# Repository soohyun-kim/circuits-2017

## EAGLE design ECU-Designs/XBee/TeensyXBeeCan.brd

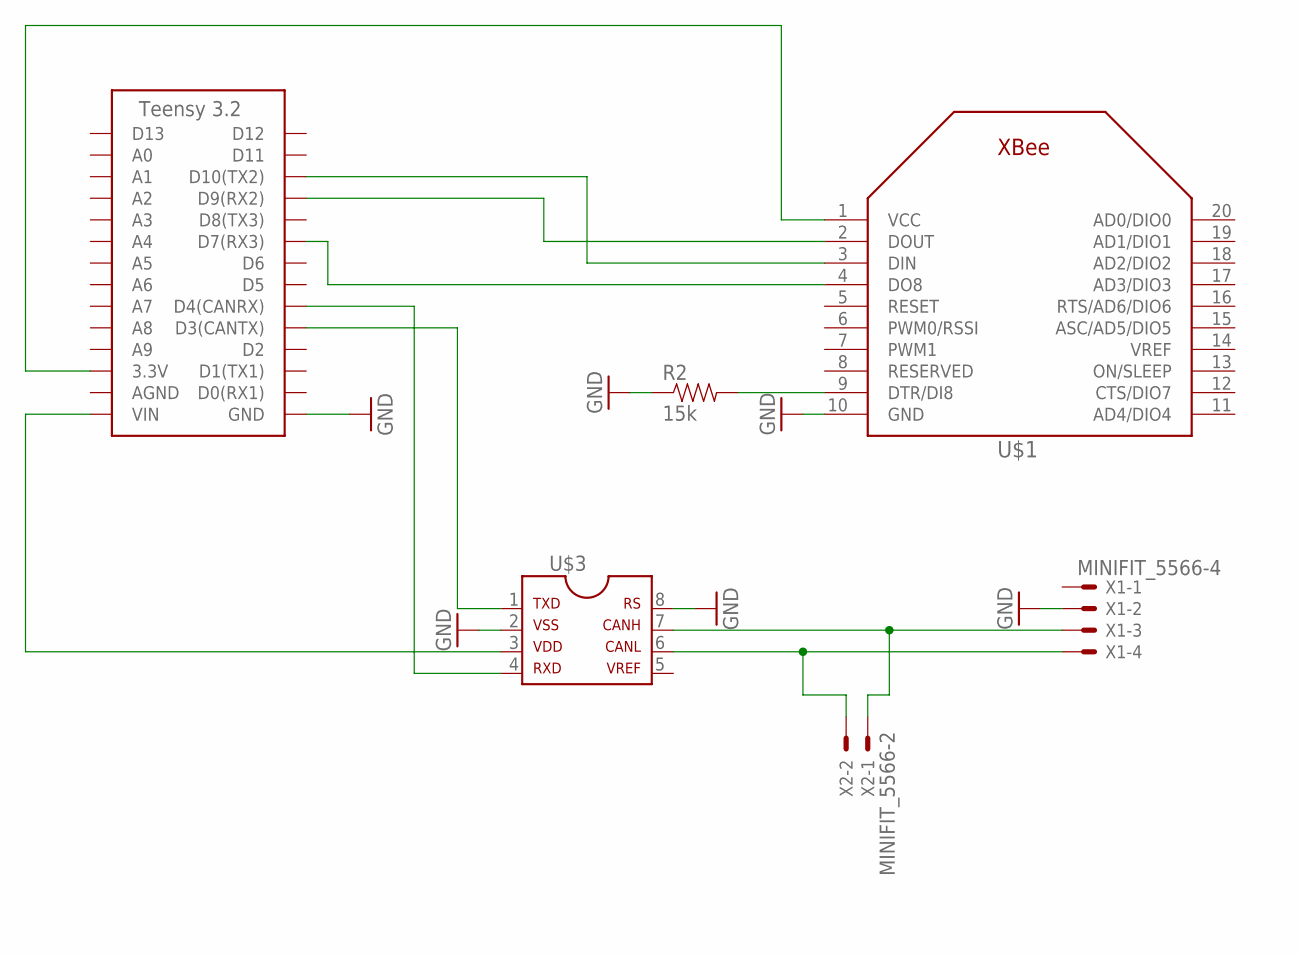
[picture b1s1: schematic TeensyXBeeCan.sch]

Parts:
R2: 15k; 0805
U$1: XBEE
U$2: TEENSY_3.2_SIMPLE
U$3: MCP2551; SOIC-08
X1: MINIFIT_5566-4
X2: MINIFIT_5566-2

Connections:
GND: R2.1, U$1.10 (GND), U$2.GND, U$3.2, U$3.8, X1.2
unnamed: U$2.VIN, U$3.3
unnamed: U$1.2 (DOUT), U$2.D9(RX2)
unnamed: U$1.3 (DIN), U$2.D10(TX2)
unnamed: U$2.D3(CANTX), U$3.1
unnamed: U$2.D4(CANRX), U$3.4
unnamed: U$3.6, X1.4, X2.2
unnamed: U$3.7, X1.3, X2.1
unnamed: U$1.4 (DO8), U$2.D7(RX3)
unnamed: R2.2, U$1.9 (DTR/DI8)
VCC: U$1.1 (VCC), U$2.3.3V

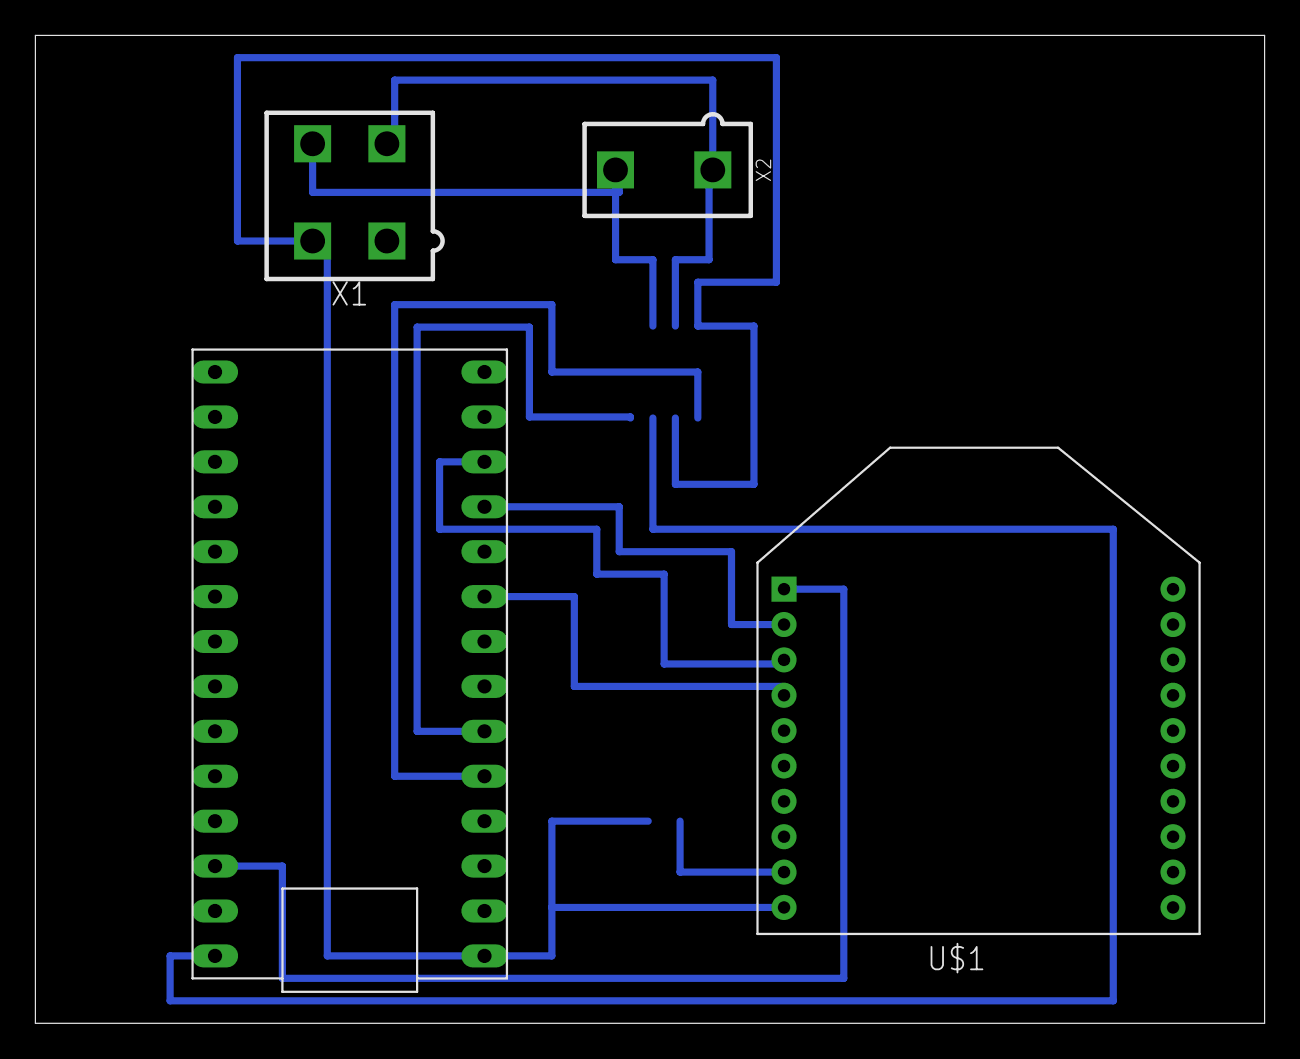
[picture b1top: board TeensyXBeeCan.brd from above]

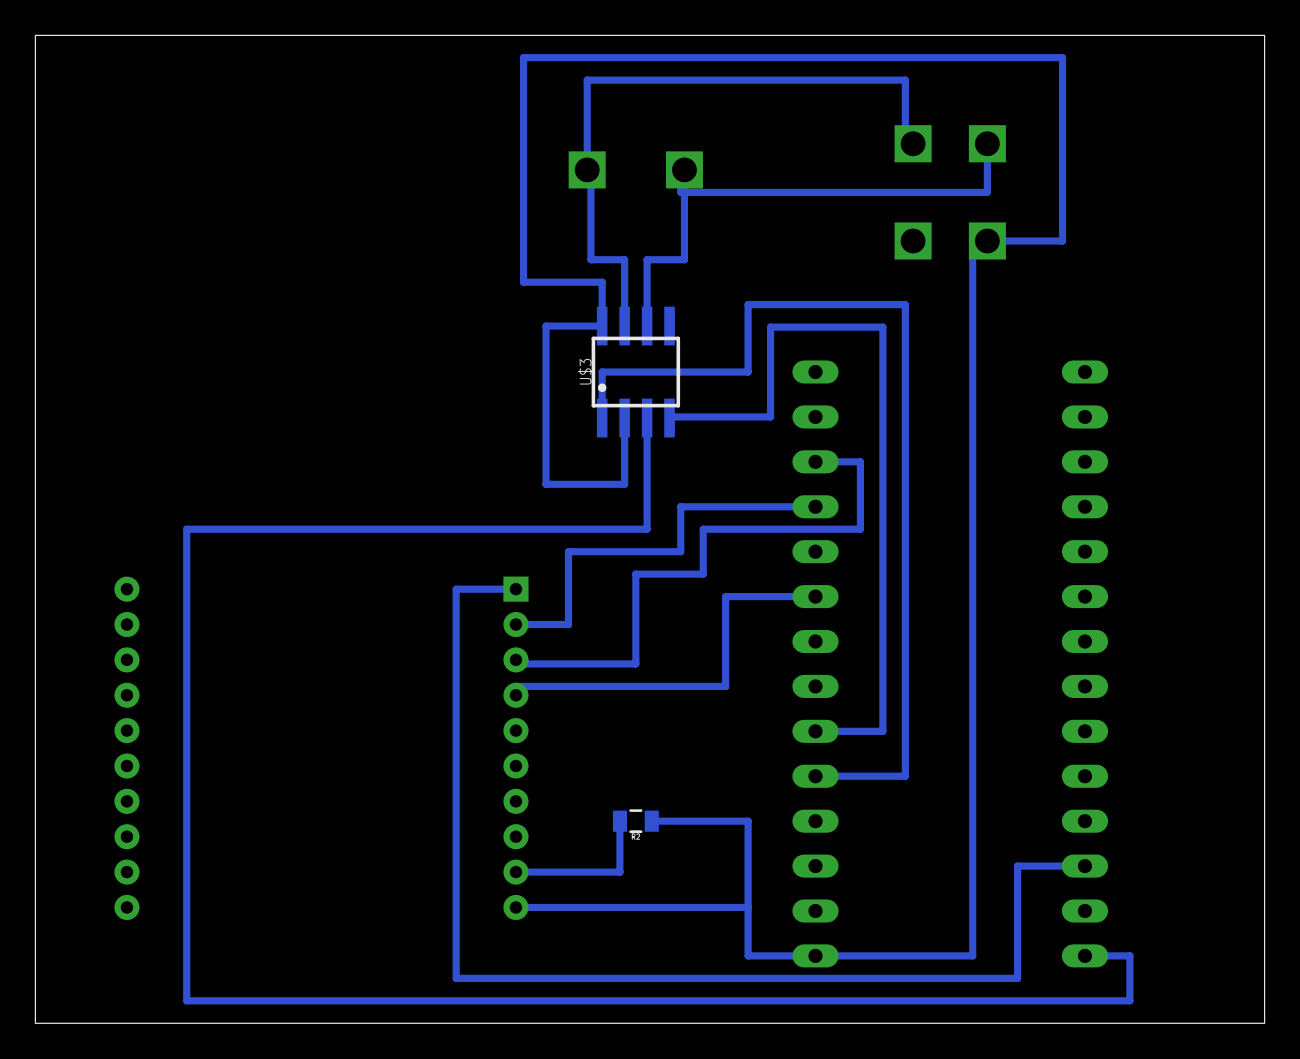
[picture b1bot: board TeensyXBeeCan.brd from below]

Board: 2 copper layers, 69.5 x 55.9 mm, 6 parts (2 on the bottom side), 11 nets.

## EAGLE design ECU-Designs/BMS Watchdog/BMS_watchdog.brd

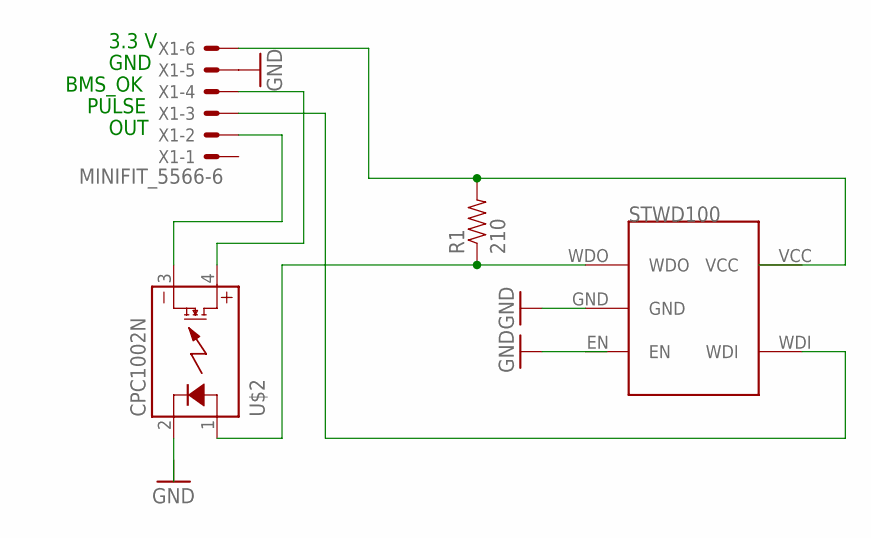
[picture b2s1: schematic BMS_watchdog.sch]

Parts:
R1: 210; 0805
U$1: STWD100; SOT23-5
U$2: CPC1002N; SOP04
X1: MINIFIT_5566-6

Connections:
GND: U$1.GND, X1.5
unnamed: R1.2, X1.6
unnamed: U$1.WDI, X1.3
unnamed: R1.1, U$1.WDO, U$2.1 (CONTROL+)
unnamed: U$2.4 (DC+), X1.4
unnamed: U$2.3 (DC-), X1.2

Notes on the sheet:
3.3 V
GND
PULSE
BMS_OK
OUT

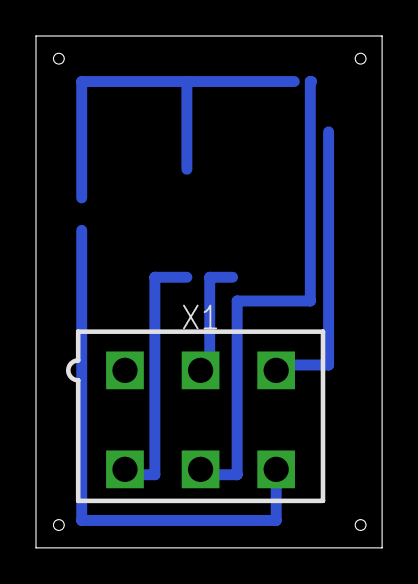
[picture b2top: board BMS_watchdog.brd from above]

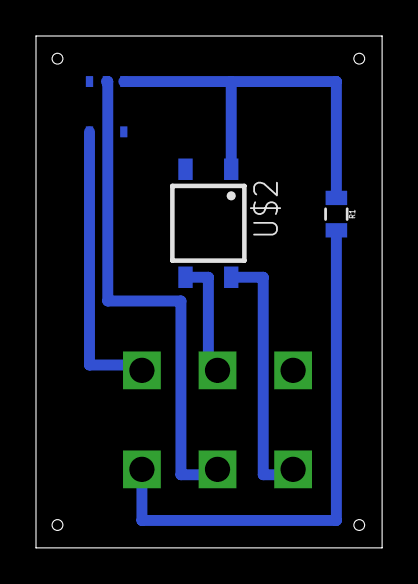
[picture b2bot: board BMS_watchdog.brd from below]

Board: 2 copper layers, 19.2 x 28.4 mm, 4 parts (3 on the bottom side), 6 nets.

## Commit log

2017-02-05 Added XBee stuff
2017-02-24 STWD100 Watchdog Timer chip
2017-02-25 Updated moter controller board with switch designation
2017-03-01 BMS watchdog schematics and board
2017-03-04 Updated BMS watchdog
